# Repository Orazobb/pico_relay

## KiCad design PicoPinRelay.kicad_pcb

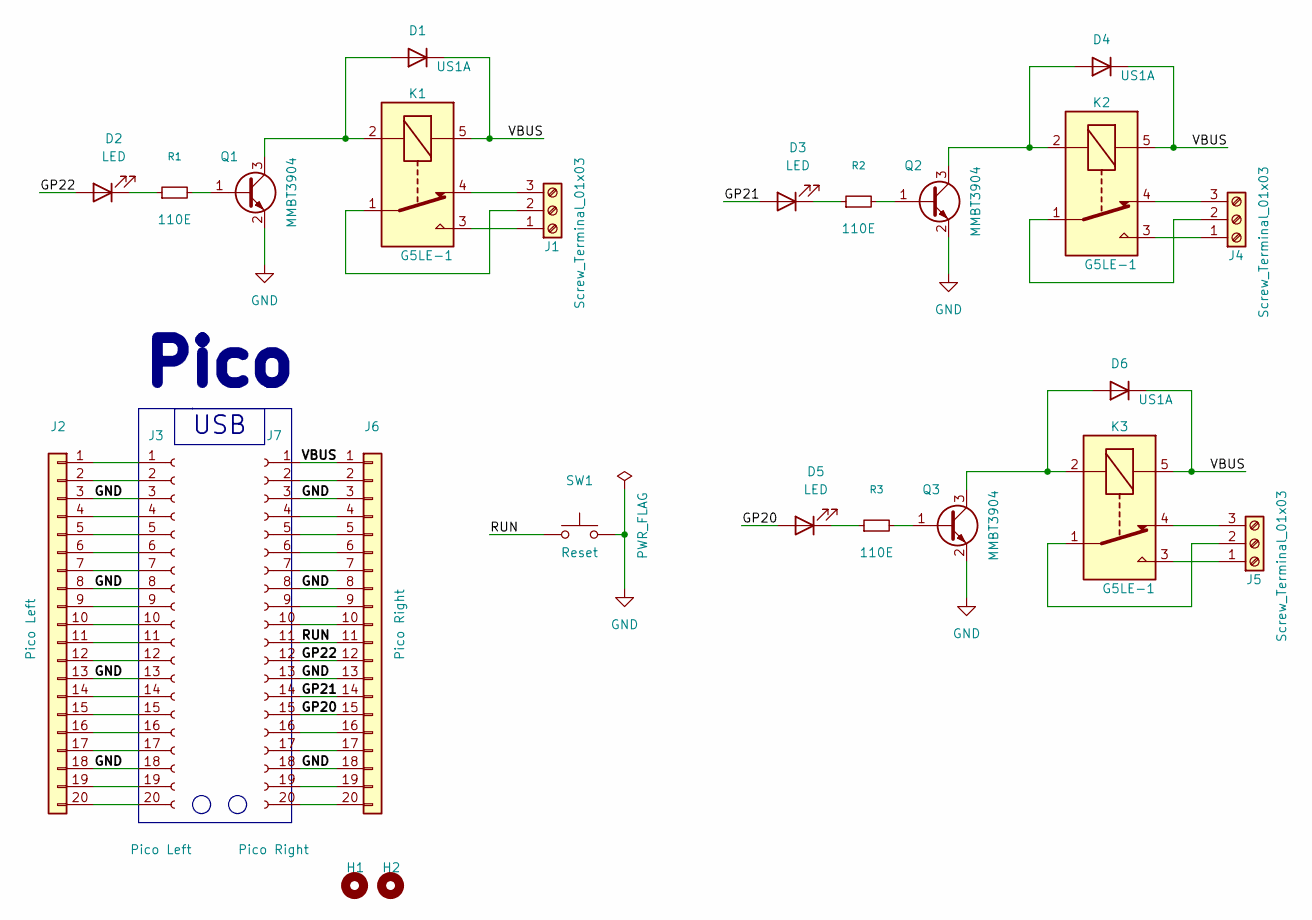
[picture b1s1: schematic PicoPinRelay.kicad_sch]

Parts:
D1, D4, D6: US1A; D_SMA
D2, D3, D5: LED; LED_0805_2012Metric
H1, H2: MountingHole; MountingHole_3.2mm_M3_DIN965_Pad_TopBottom
J1, J4, J5: Screw_Terminal_01x03; TerminalBlock_Phoenix_MPT-0,5-3-2.54_1x03_P2.54mm_Horizontal
J2: Pico Left; PinHeader_1x20_P2.54mm_Vertical
J3: Pico Left; PinSocket_1x20_P2.54mm_Vertical
J6: Pico Right; PinHeader_1x20_P2.54mm_Vertical
J7: Pico Right; PinSocket_1x20_P2.54mm_Vertical
K1, K2, K3: G5LE-1; Relay_SPDT_Omron-G5LE-1
Q1, Q2, Q3: MMBT3904; SOT-23
R1, R2, R3: 110E; R_0805_2012Metric_Pad1.20x1.40mm_HandSolder
SW1: Reset; SW_SPST_B3U-1000P

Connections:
/GP20: D5.2 (A), J6.15, J7.15
/GP21: D3.2 (A), J6.14, J7.14
/GP22: D2.2 (A), J6.12, J7.12
/RUN: J6.11, J7.11, SW1.1
/VBUS: D1.1 (K), D4.1 (K), D6.1 (K), J6.1, J7.1, K1.5, K2.5, K3.5
GND: J2.3, J2.8, J2.13, J2.18, J3.3, J3.8, J3.13, J3.18, J6.3, J6.8, J6.13, J6.18, J7.3, J7.8, J7.13, J7.18, Q1.2 (E), Q2.2 (E), Q3.2 (E), SW1.2
unnamed: D1.2 (A), K1.2, Q1.3 (C)
unnamed: D2.1 (K), R1.1
unnamed: D3.1 (K), R2.1
unnamed: D4.2 (A), K2.2, Q2.3 (C)
unnamed: D5.1 (K), R3.1
unnamed: D6.2 (A), K3.2, Q3.3 (C)
unnamed: J1.1, K1.3
unnamed: J1.2, K1.1
unnamed: J1.3, K1.4
unnamed: J2.1, J3.1
unnamed: J2.2, J3.2
unnamed: J2.4, J3.4
unnamed: J2.5, J3.5
unnamed: J2.6, J3.6
unnamed: J2.7, J3.7
unnamed: J2.9, J3.9
unnamed: J2.10, J3.10
unnamed: J2.11, J3.11
unnamed: J2.12, J3.12
unnamed: J2.14, J3.14
unnamed: J2.15, J3.15
unnamed: J2.16, J3.16
unnamed: J2.17, J3.17
unnamed: J2.19, J3.19
unnamed: J2.20, J3.20
unnamed: J4.1, K2.3
unnamed: J4.2, K2.1
unnamed: J4.3, K2.4
unnamed: J5.1, K3.3
unnamed: J5.2, K3.1
unnamed: J5.3, K3.4
unnamed: J6.2, J7.2
unnamed: J6.4, J7.4
unnamed: J6.5, J7.5
unnamed: J6.6, J7.6
unnamed: J6.7, J7.7
unnamed: J6.9, J7.9
unnamed: J6.10, J7.10
unnamed: J6.16, J7.16
unnamed: J6.17, J7.17
unnamed: J6.19, J7.19
unnamed: J6.20, J7.20
unnamed: Q1.1 (B), R1.2
unnamed: Q2.1 (B), R2.2
unnamed: Q3.1 (B), R3.2

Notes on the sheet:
USB
Pico

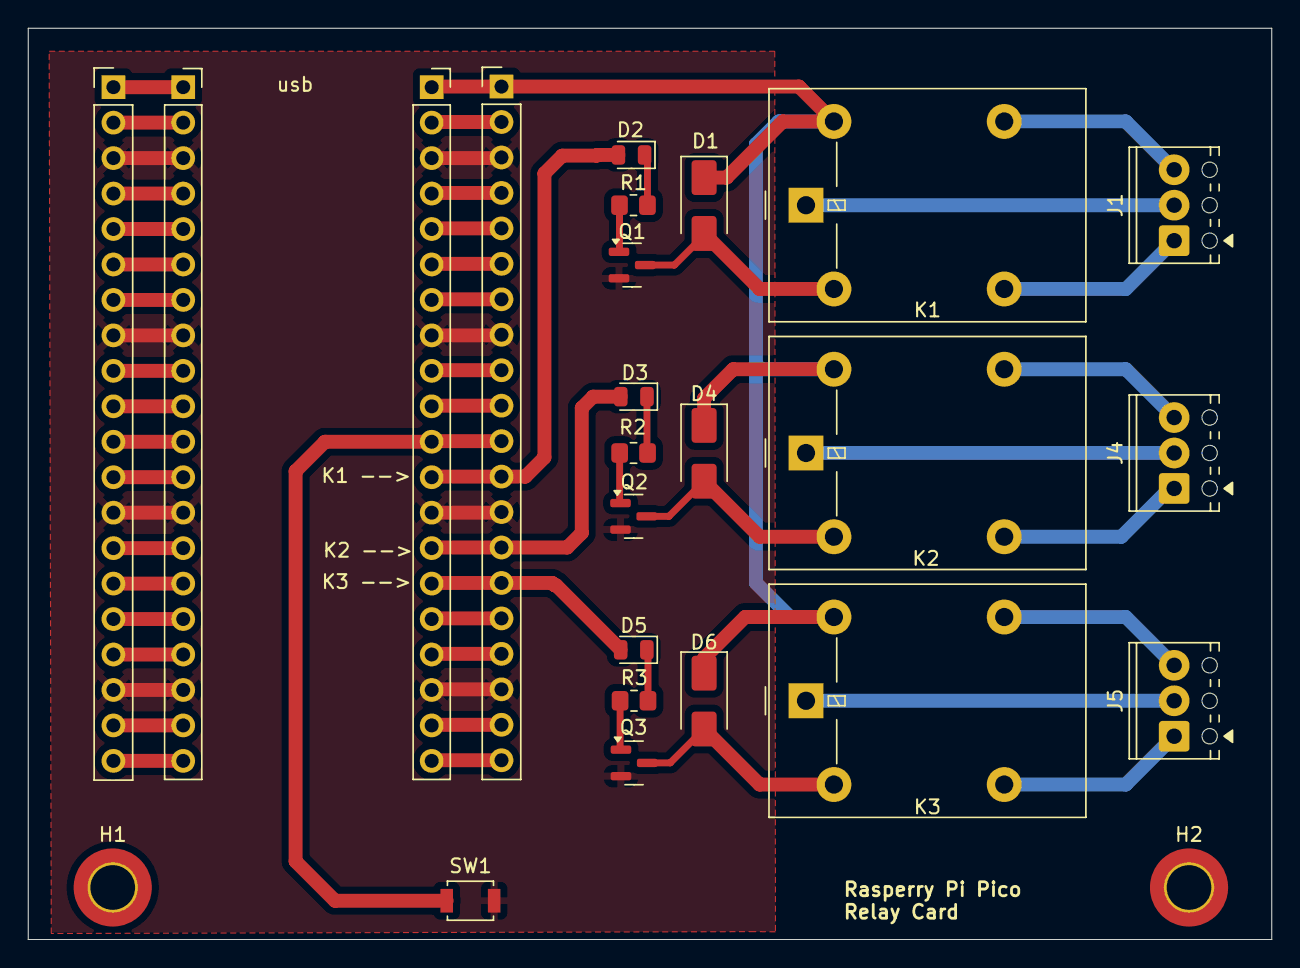
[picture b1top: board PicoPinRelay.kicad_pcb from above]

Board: 2 copper layers, 89.1 x 65.3 mm, 25 parts (0 on the bottom side), 51 nets.
